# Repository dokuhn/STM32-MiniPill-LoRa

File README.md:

# STM32-MiniPill-LoRa 

## Schematic

## License 

This work is licensed under a
[Creative Commons Attribution-NonCommercial-ShareAlike 4.0 International License][cc-by-nc-sa].

[![CC BY-NC-SA 4.0][cc-by-nc-sa-image]][cc-by-nc-sa]

[cc-by-nc-sa]: http://creativecommons.org/licenses/by-nc-sa/4.0/
[cc-by-nc-sa-image]: https://licensebuttons.net/l/by-nc-sa/4.0/88x31.png
[cc-by-nc-sa-shield]: https://img.shields.io/badge/License-CC%20BY--NC--SA%204.0-lightgrey.svg

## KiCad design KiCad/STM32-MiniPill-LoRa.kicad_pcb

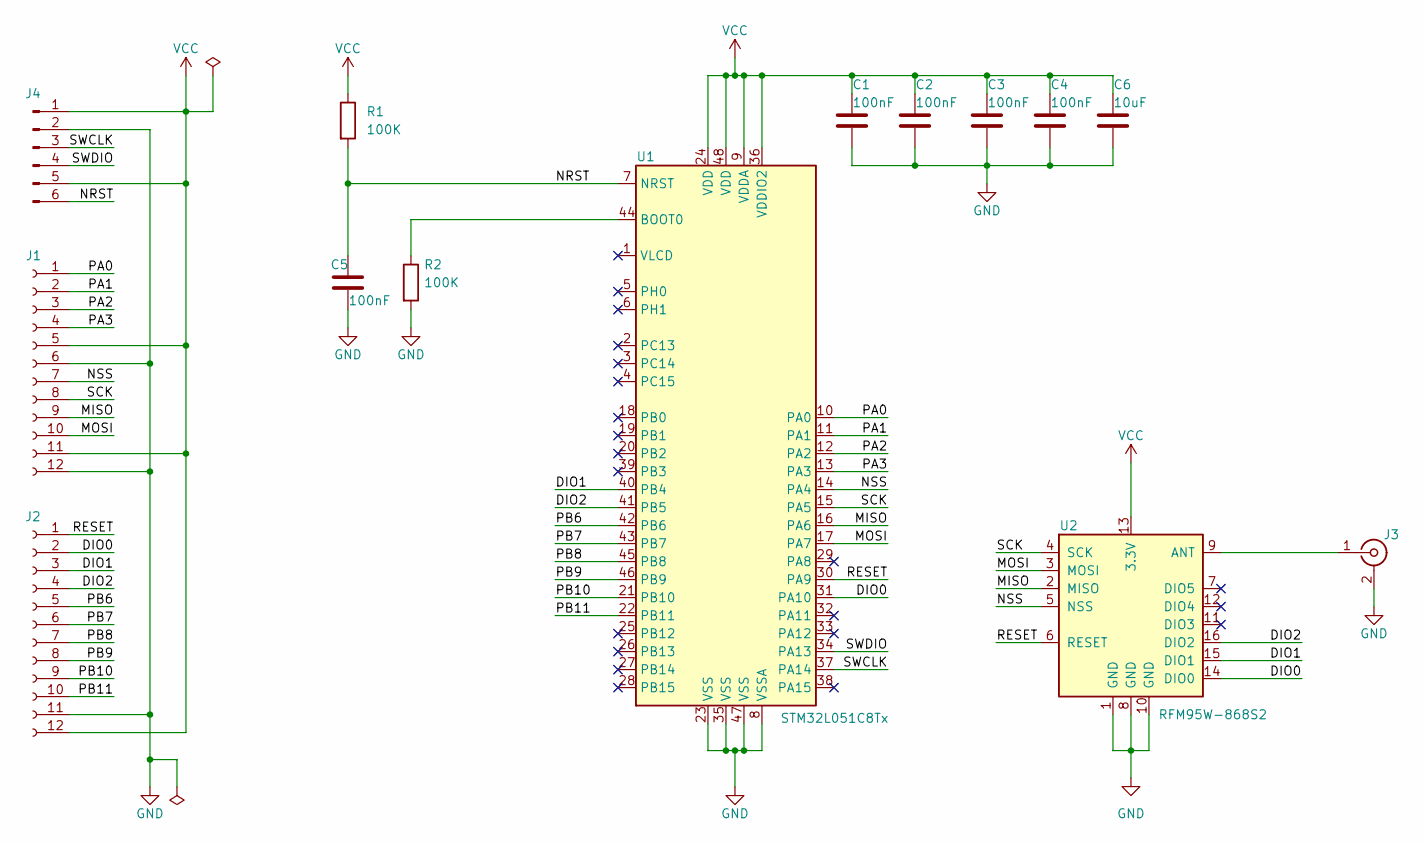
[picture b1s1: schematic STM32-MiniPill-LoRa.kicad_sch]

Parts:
C1, C2, C3, C4, C5: 100nF; C_0603_1608Metric
C6: 10uF; C_0805_2012Metric
J1, J2: Conn_01x12_Female; PinSocket_1x12_P2.54mm_Vertical
J3: Conn_Coaxial; SMA_Molex_73251-1153_EdgeMount_Horizontal
J4: Conn_01x06_Male; PinHeader_1x06_P2.54mm_Horizontal
R1, R2: 100K; R_0603_1608Metric
U1: STM32L051C8Tx; LQFP-48_7x7mm_P0.5mm
U2: RFM95W-868S2; HOPERF_RFM9XW_SMD

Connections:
/DIO0: J2.2, U1.31 (PA10), U2.14 (DIO0)
/DIO1: J2.3, U1.40 (PB4), U2.15 (DIO1)
/DIO2: J2.4, U1.41 (PB5), U2.16 (DIO2)
/MISO: J1.9, U1.16 (PA6), U2.2 (MISO)
/MOSI: J1.10, U1.17 (PA7), U2.3 (MOSI)
/NRST: C5.1, J4.6, R1.2, U1.7 (NRST)
/NSS: J1.7, U1.14 (PA4), U2.5 (NSS)
/PA0: J1.1, U1.10 (PA0)
/PA1: J1.2, U1.11 (PA1)
/PA2: J1.3, U1.12 (PA2)
/PA3: J1.4, U1.13 (PA3)
/PB6: J2.5, U1.42 (PB6)
/PB7: J2.6, U1.43 (PB7)
/PB8: J2.7, U1.45 (PB8)
/PB9: J2.8, U1.46 (PB9)
/PB10: J2.9, U1.21 (PB10)
/PB11: J2.10, U1.22 (PB11)
/RESET: J2.1, U1.30 (PA9), U2.6 (RESET)
/SCK: J1.8, U1.15 (PA5), U2.4 (SCK)
/SWCLK: J4.3, U1.37 (PA14)
/SWDIO: J4.4, U1.34 (PA13)
GND: C1.2, C2.2, C3.2, C4.2, C5.2, C6.2, J1.6, J1.12, J2.11, J3.2 (Ext), J4.2, R2.2, U1.8 (VSSA), U1.23 (VSS), U1.35 (VSS), U1.47 (VSS), U2.1 (GND), U2.8 (GND), U2.10 (GND)
unnamed: J3.1 (In), U2.9 (ANT)
unnamed: R2.1, U1.44 (BOOT0)
VCC: C1.1, C2.1, C3.1, C4.1, C6.1, J1.5, J1.11, J2.12, J4.1, J4.5, R1.1, U1.9 (VDDA), U1.24 (VDD), U1.36 (VDDIO2), U1.48 (VDD), U2.13 (3.3V)

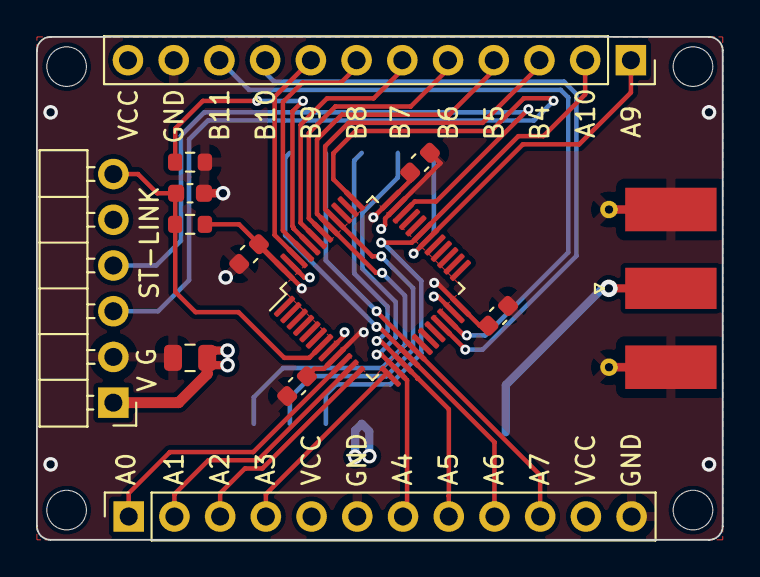
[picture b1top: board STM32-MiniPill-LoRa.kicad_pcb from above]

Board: 4 copper layers, 38.1 x 27.9 mm, 14 parts (1 on the bottom side), 25 nets.

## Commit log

2023-09-27 adding ST-Link Connector
2023-10-13 adding 3D Models of SMA Molex Connector
2023-10-15 first time every trace routed
2023-10-22 last modification before push to GitHub
2023-10-30 fist order
2023-11-22 update README file
2023-11-23 fixing error in README file
